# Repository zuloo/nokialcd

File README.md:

# nokialcd

### Python Class to use a Nokia 6100  Display with Epson Controller on a Raspberry Pi

There is also some stuff for the Phillips Controller, but I lack a
Display with that Controller to test it.

Have a look at test.py to see an usage example

I use native SPI to communicate with the Display - no Bitbanging -
but I have to use 2 byte for every 9-bit-word the display expects.

Performance is ok, but do not expect more than 1/2 to 1 FPS.

### Additional material

I also added some Eagel Files from Sparkfun in the PCB folder
so you can produce a Breakout PCB,since it no longer available on Sparkfun.

The Datasheets can be found in DATASHEET as well, as an excellant Documentation from
James P. Lynch, which helped me a lot getting this thing to work properly.

### Wiring

If you use the Sparkfun Board connect the Pins as Follow

| RPi      | PCB   |
|----------|-------|
| MOSI     | DIO   |
| SCLK     | SCK   |
| CS1      | CS    |
| GPIO #21 | RESET |
| GND      | GND   |
| 3.3V     | 3.3V  |
| 5V       | VBATT |

that should do it

### License
License is MIT or something.

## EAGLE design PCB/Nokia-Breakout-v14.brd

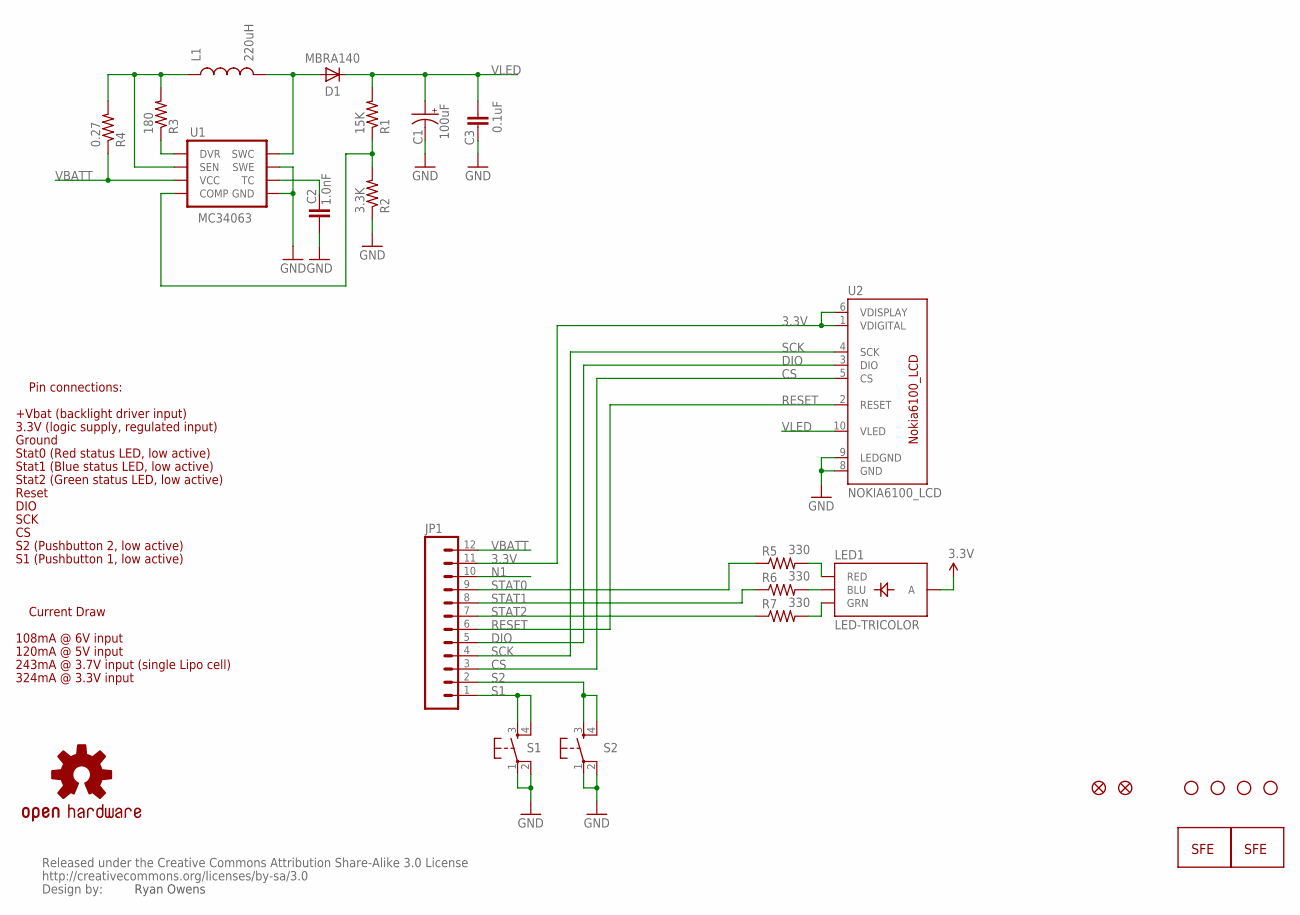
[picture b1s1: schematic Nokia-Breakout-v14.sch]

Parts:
C1: 100uF; EIA7343
C2: 1.0nF; 0402-CAP
C3: 0.1uF; 0402-CAP
D1: MBRA140; SMA-DIODE
JP1: M12PTH; 1X12
JP2, JP3: FIDUCIALUFIDUCIAL; MICRO-FIDUCIAL
L1: 220uH; NPI75C
LED1: LED-TRICOLOR; LED-TRICOLOR-SMD
R1: 15K; 0402-RES
R2: 3.3K; 0402-RES
R3: 180; 0402-RES
R4: 0.27; 0402-RES
R5, R6, R7: 330; 0402-RES
S1, S2: TAC_SWITCHSMD; TACTILE_SWITCH_SMD
U1: MC34063; SO08
U2: NOKIA6100_LCD
U$1, U$2, U$3, U$5: STAND-OFF
U$8: LOGO-SFENEW; SFE-NEW-WEBLOGO
U$9: OSHW-LOGOS; OSHW-LOGO-S
U$10: CREATIVE_COMMONS
U$12: LOGO-SFESK; SFE-LOGO-FLAME

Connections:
3.3V: JP1.11, LED1.A, U2.1 (VDIGITAL), U2.6 (VDISPLAY)
CS: JP1.3, U2.5 (CS)
DIO: JP1.5, U2.3 (DIO)
N1: C1.C (-), C2.2, C3.2, JP1.10, R2.1, S1.1, S1.2, S2.1, S2.2, U1.2 (SWE), U1.4 (GND), U2.8 (GND), U2.9 (LEDGND)
unnamed: LED1.R (RED), R5.2
unnamed: D1.A, L1.2, U1.1 (SWC)
unnamed: L1.1, R3.2, R4.2, U1.7 (SEN)
unnamed: R3.1, U1.8 (DVR)
unnamed: R1.1, R2.2, U1.5 (COMP)
unnamed: C2.1, U1.3 (TC)
unnamed: LED1.G (GRN), R7.2
unnamed: LED1.B (BLU), R6.2
RESET: JP1.6, U2.2 (RESET)
S1: JP1.1, S1.3, S1.4
S2: JP1.2, S2.3, S2.4
SCK: JP1.4, U2.4 (SCK)
STAT0: JP1.9, R5.1
STAT1: JP1.8, R6.1
STAT2: JP1.7, R7.1
VBATT: JP1.12, R4.1, U1.6 (VCC)
VLED: C1.A (+), C3.1, D1.C, R1.2, U2.10 (VLED)

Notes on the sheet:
Ryan Owens
Pin connections:
+Vbat (backlight driver input)
3.3V (logic supply, regulated input)
Ground
Stat0 (Red status LED, low active)
Stat1 (Blue status LED, low active)
Stat2 (Green status LED, low active)
Reset
DIO
SCK
S2 (Pushbutton 2, low active)
S1 (Pushbutton 1, low active)
Current Draw
108mA @ 6V input
120mA @ 5V input
243mA @ 3.7V input (single Lipo cell)
324mA @ 3.3V input

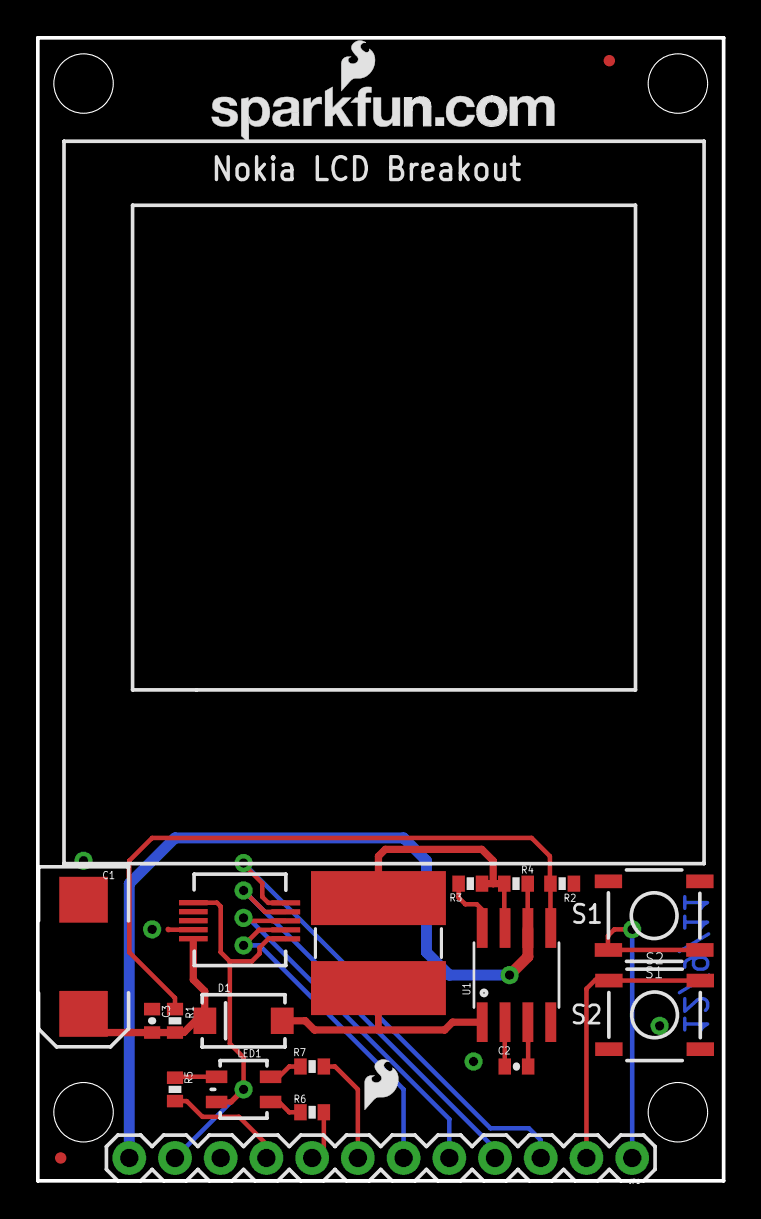
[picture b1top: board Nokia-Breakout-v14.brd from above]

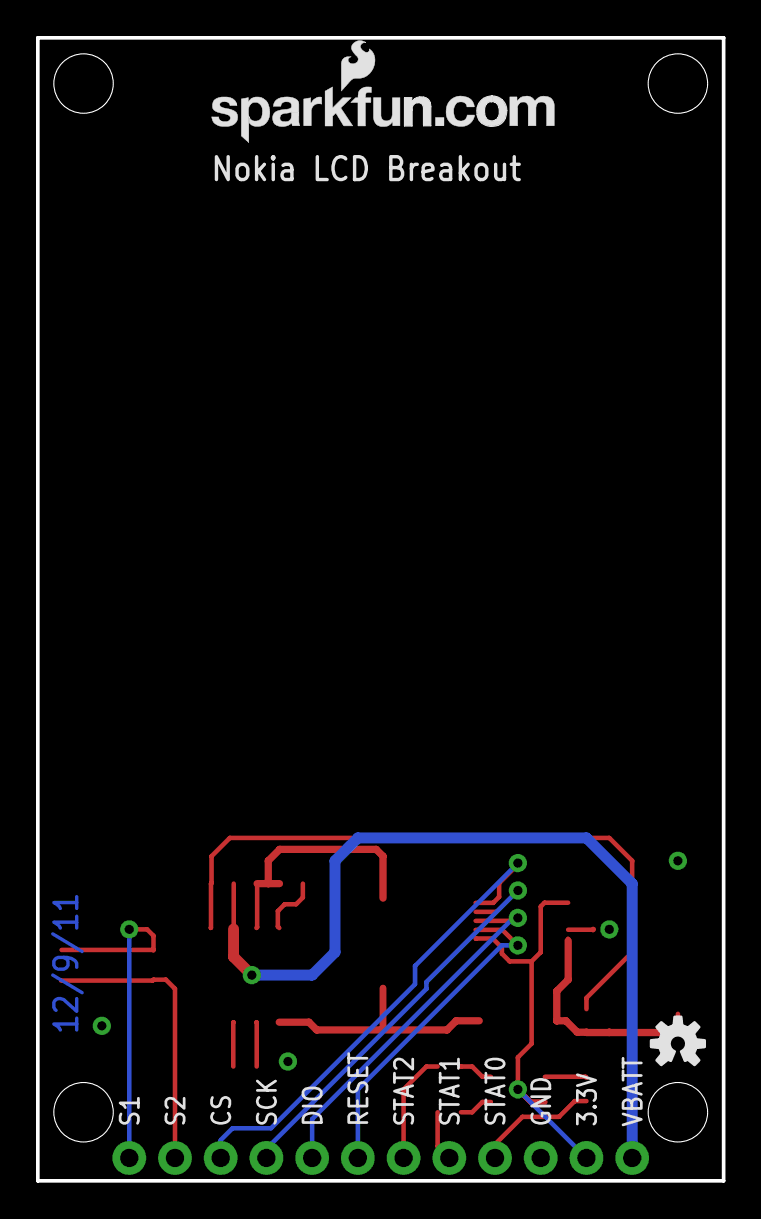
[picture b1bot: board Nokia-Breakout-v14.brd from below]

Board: 2 copper layers, 38.1 x 63.5 mm, 29 parts (2 on the bottom side), 21 nets.

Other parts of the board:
U$4: LOGO-SFENEW; SFE-NEW-WEBLOGO

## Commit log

2016-10-29 initial release
2016-10-29 additional infos
2016-10-29 table foo

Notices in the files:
parts and their libraries:
SparkFun: Released under the Creative Commons Attribution Share-Alike 3.0 License
SparkFun: http://creativecommons.org/licenses/by-sa/3.0
